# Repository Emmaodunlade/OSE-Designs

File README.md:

# OSE-Designs
 Contributions to OSE #OpenHardware

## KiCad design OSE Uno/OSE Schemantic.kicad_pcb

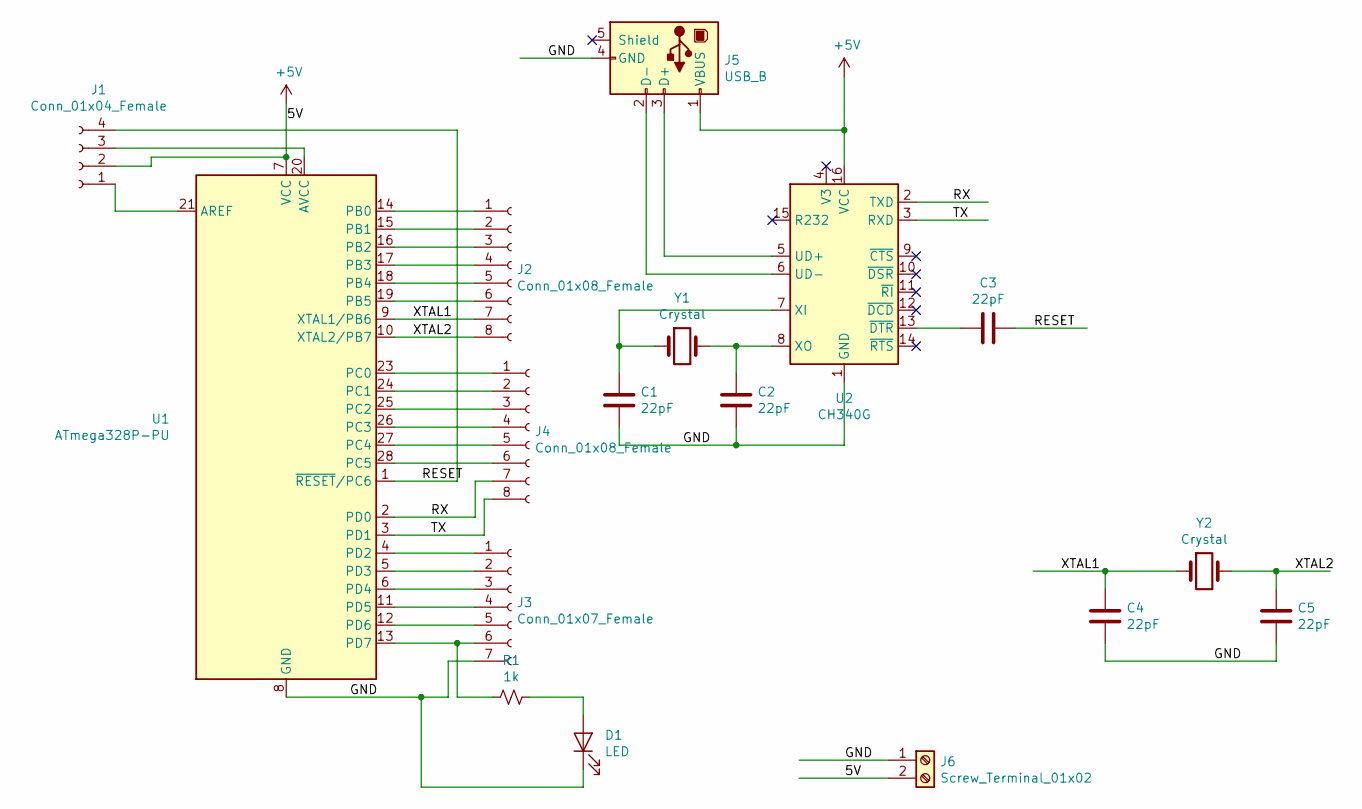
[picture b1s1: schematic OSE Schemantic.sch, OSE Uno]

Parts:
C1, C2, C3, C4, C5: 22pF; CP_Elec_3x5.3
D1: LED; LED_D5.0mm
J1: Conn_01x04_Female; PinHeader_1x04_P1.00mm_Vertical
J2, J4: Conn_01x08_Female; PinHeader_1x08_P1.00mm_Vertical
J3: Conn_01x07_Female; PinHeader_1x07_P1.00mm_Vertical
J5: USB_B; USB3_A_Plug_Wuerth_692112030100_Horizontal
J6: Screw_Terminal_01x02; Altech_AK300_1x02_P5.00mm_45-Degree
R1: 1k; R_Axial_DIN0207_L6.3mm_D2.5mm_P7.62mm_Horizontal
U1: ATmega328P-PU; DIP-28_W7.62mm
U2: CH340G; SOIC-16_3.9x9.9mm_P1.27mm
Y1, Y2: Crystal; Crystal_HC49-4H_Vertical

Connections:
+5V: J1.2, J5.1 (VBUS), J6.2, U1.7 (VCC), U2.16 (VCC)
/GND: C1.2, C2.2, C4.2, C5.2, D1.1 (K), J3.7, J5.4 (GND), J6.1, U1.8 (GND), U1.22 (GND), U2.1 (GND)
/RESET: C3.2, J1.4, U1.1 (~RESET~/PC6)
/RX: J4.7, U1.2 (PD0), U2.2 (TXD)
/TX: J4.8, U1.3 (PD1), U2.3 (RXD)
/XTAL1: C4.1, J2.7, U1.9 (XTAL1/PB6), Y2.1
/XTAL2: C5.1, J2.8, U1.10 (XTAL2/PB7), Y2.2
unnamed: C1.1, U2.7 (XI), Y1.1
unnamed: C2.1, U2.8 (XO), Y1.2
unnamed: C3.1, U2.13 (~DTR)
unnamed: D1.2 (A), R1.1
unnamed: J1.1, U1.21 (AREF)
unnamed: J1.3, U1.20 (AVCC)
unnamed: J2.1, U1.14 (PB0)
unnamed: J2.2, U1.15 (PB1)
unnamed: J2.3, U1.16 (PB2)
unnamed: J2.4, U1.17 (PB3)
unnamed: J2.5, U1.18 (PB4)
unnamed: J2.6, U1.19 (PB5)
unnamed: J3.1, U1.4 (PD2)
unnamed: J3.2, U1.5 (PD3)
unnamed: J3.3, U1.6 (PD4)
unnamed: J3.4, U1.11 (PD5)
unnamed: J3.5, U1.12 (PD6)
unnamed: J3.6, R1.2, U1.13 (PD7)
unnamed: J4.1, U1.23 (PC0)
unnamed: J4.2, U1.24 (PC1)
unnamed: J4.3, U1.25 (PC2)
unnamed: J4.4, U1.26 (PC3)
unnamed: J4.5, U1.27 (PC4)
unnamed: J4.6, U1.28 (PC5)
unnamed: J5.2 (D-), U2.6 (UD-)
unnamed: J5.3 (D+), U2.5 (UD+)

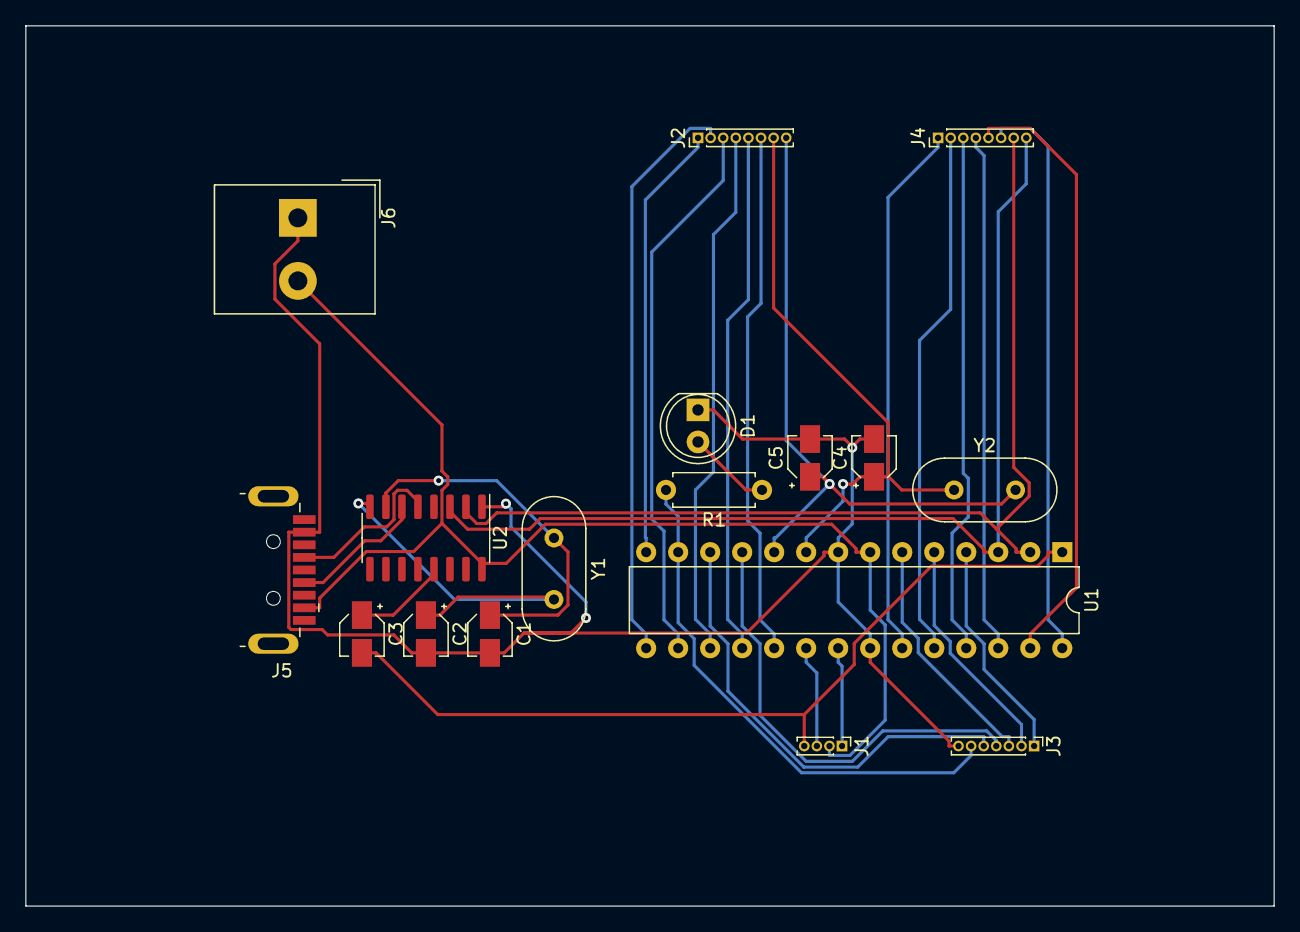
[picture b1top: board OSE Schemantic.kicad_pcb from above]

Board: 2 copper layers, 99.1 x 69.8 mm, 17 parts (0 on the bottom side), 33 nets.

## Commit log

2019-10-28 Schematics and Board Designs with Eagle
    V3 Commit
2019-10-29 3D View added
    Adding the 3D image
